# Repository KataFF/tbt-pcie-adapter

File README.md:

# Thunderbolt to PCIe Adapter

Copyright (c) 2022-2024 [Antmicro](https://www.antmicro.com) 
Original design by Antmicro up to rev. 1.0.2.
Further developed by Kajetan Wierszelis (rev. 1.0.3. and later ones)

## Overview

This project contains open hardware design files for an adapter board wrapping 4-lane (i.e. 4x) PCIe Gen 3.0 devices into a Thunderbolt 3 uplink.
It is based on the Intel/JHL6340SLLSQ Thunderbolt controller.
The design files were prepared in KiCad 7.x & updated to KiCad 8.x.

## Key features

* Intel JHL6340SLLSQ Thunderbolt 3 controller 
* PCIe x4 expansion slot
* On-board Step-Up DC-DC generating 12V (required by some PCIe cards)

## Project structure

The main directory contains KiCad PCB project files, a LICENSE, and a README.
The remaining files are stored in the following directories:

* `img` - contains graphics for this README
* `doc` - contains schematics in pdf form
* `assets` - contains visual assets for showcasing the board at [Open Hardware Portal](https://openhardware.antmicro.com)

## Licensing

This project is published under the [Apache-2.0](LICENSE) license.

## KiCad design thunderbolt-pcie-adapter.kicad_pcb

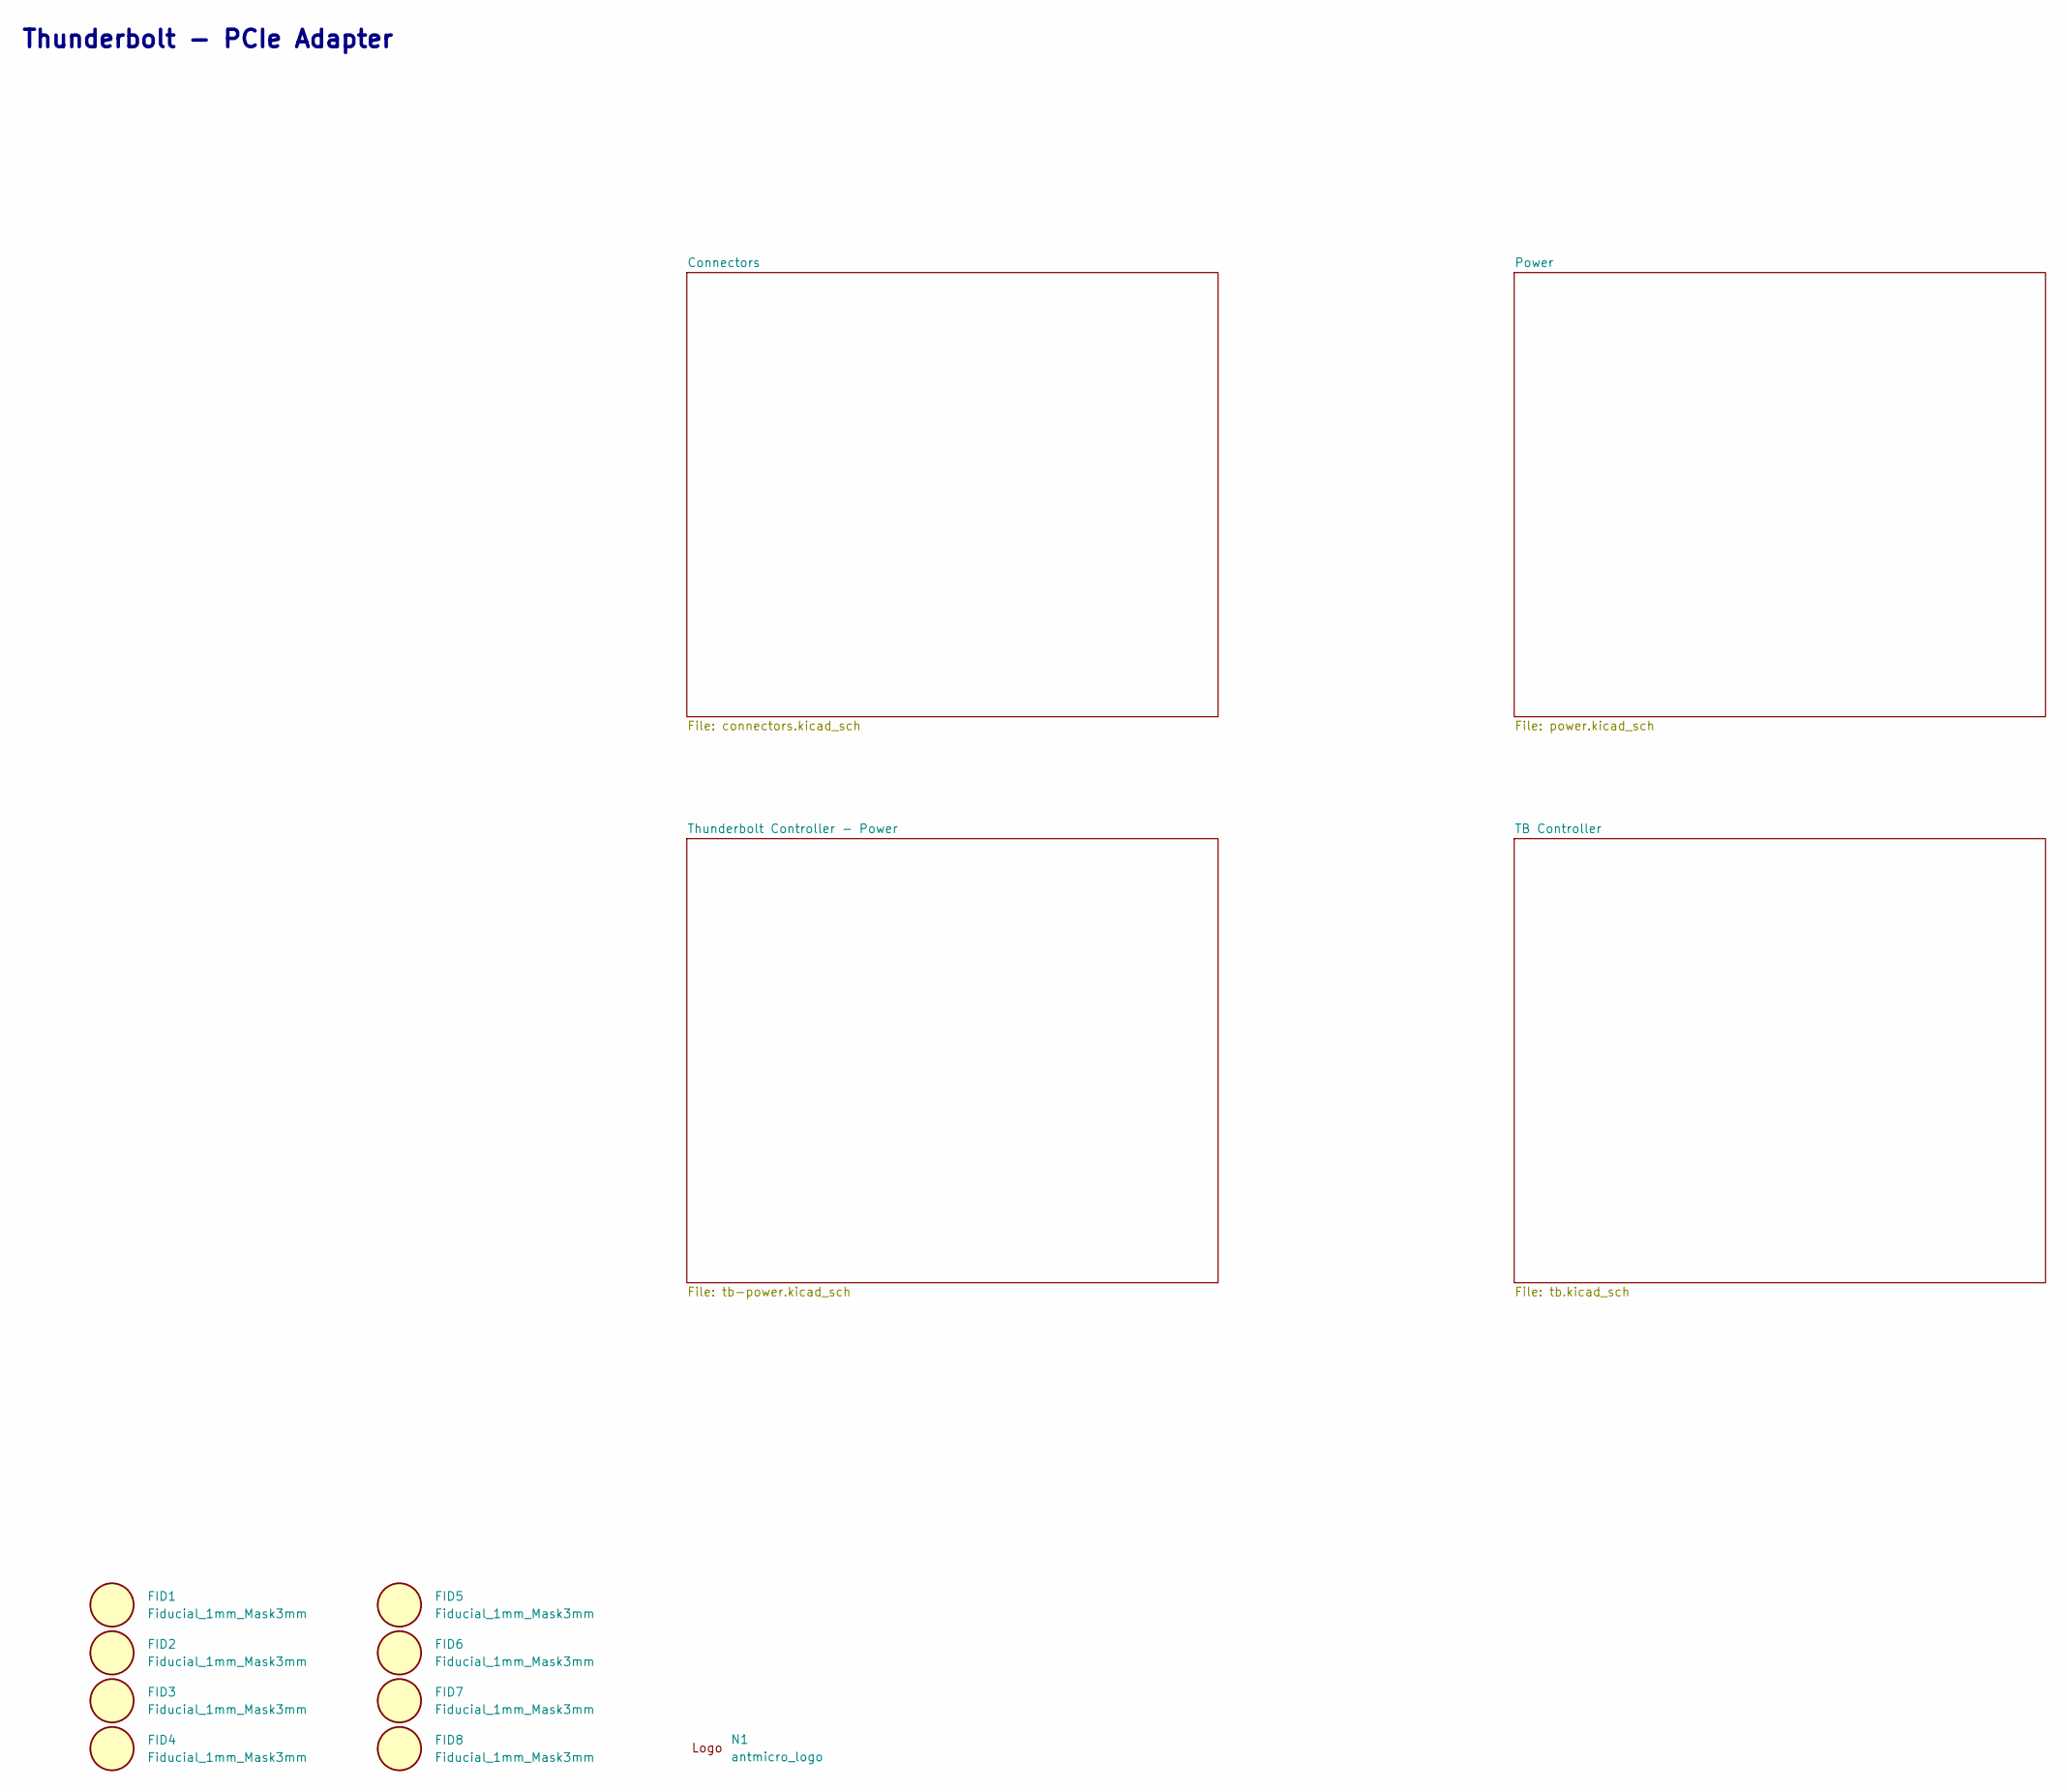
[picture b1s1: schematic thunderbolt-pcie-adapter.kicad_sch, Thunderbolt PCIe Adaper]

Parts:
FID1, FID2, FID3, FID4, FID5, FID6, FID7, FID8: Fiducial_1mm_Mask3mm
N1: antmicro_logo; antmicro-logo_scaled_12mm_mask

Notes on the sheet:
Thunderbolt - PCIe Adapter

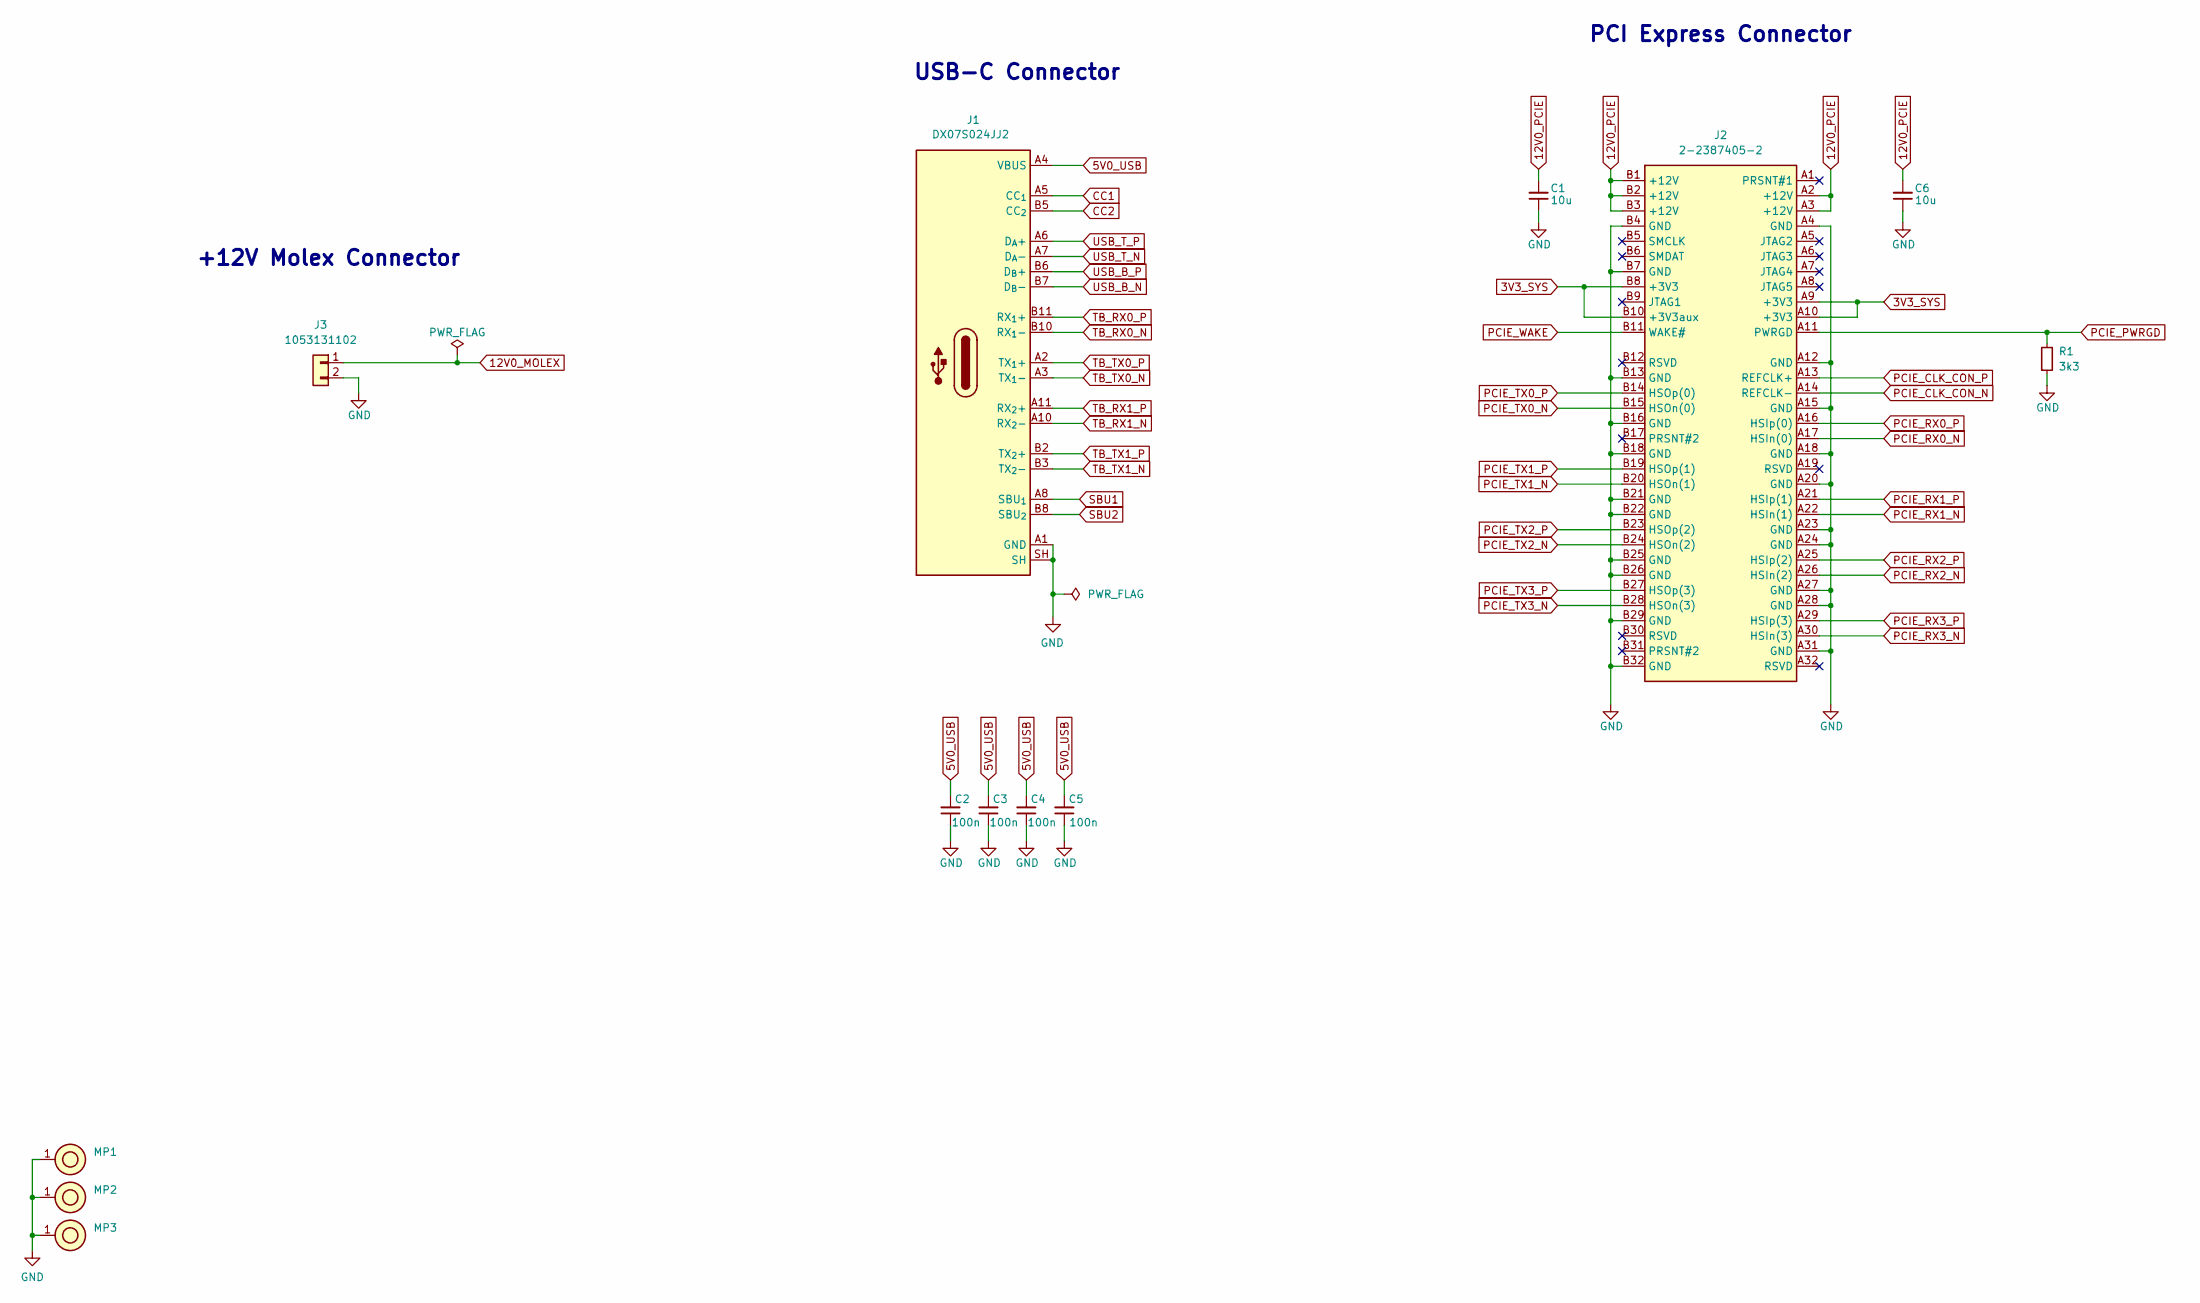
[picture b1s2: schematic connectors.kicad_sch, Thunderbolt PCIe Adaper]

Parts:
C1, C6: C_10u_0805_35V; C_0805_2012Metric; Voltage 35V; MPN GRM21BR6YA106KE43L
C2, C3, C4, C5: C_100n_0402; C_0402_1005Metric; Voltage 50V; MPN GRM155R61H104KE14D
J1: USB-C_JAE_DX07S024JJ2; USB-C_Receptacle_JAE_DX07S024JJ2; MPN DX07S024JJ2
J2: PCIe_x4_Conn_EdgeMount_Open; PCIE_TE_2-2387405-2; MPN 2-2387405-2
J3: Molex_Nano-Fit_1x2_1053131102; Conn_Molex_Nano-Fit_1x2_1053131102; MPN 1053131102
MP1, MP2, MP3: MP_Pad6mm_Drill3mm
R1: R_3k3_0402; R_0402_1005Metric; Tolerance 1%; MPN CR0402-FX-3301GLF

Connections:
3V3_SYS: J2.A9 (+3V3), J2.A10 (+3V3), J2.B8 (+3V3), J2.B10 (+3V3aux); also elsewhere on the board
5V0_USB: C2.2, C3.2, C4.2, C5.2, J1.A4 (VBUS), J1.A9 (VBUS), J1.B4 (VBUS), J1.B9 (VBUS); also elsewhere on the board
12V0_MOLEX: J3.1; also elsewhere on the board
12V0_PCIE: C1.2, C6.2, J2.A2 (+12V), J2.A3 (+12V), J2.B1 (+12V), J2.B2 (+12V), J2.B3 (+12V); also elsewhere on the board
CC1: J1.A5 (CC_{1}); also elsewhere on the board
CC2: J1.B5 (CC_{2}); also elsewhere on the board
GND: C1.1, C2.1, C3.1, C4.1, C5.1, C6.1, J1.A1 (GND), J1.A12 (GND), J1.B1 (GND), J1.B12 (GND), J1.SH, J2.A4 (GND), J2.A12 (GND), J2.A15 (GND), J2.A18 (GND), J2.A20 (GND), J2.A23 (GND), J2.A24 (GND), J2.A27 (GND), J2.A28 (GND), J2.A31 (GND), J2.B4 (GND), J2.B7 (GND), J2.B13 (GND), J2.B16 (GND), J2.B18 (GND), J2.B21 (GND), J2.B22 (GND), J2.B25 (GND), J2.B26 (GND), J2.B29 (GND), J2.B32 (GND), J3.2, MP1.1, MP2.1, MP3.1, R1.1; also elsewhere on the board
PCIE_CLK_CON_N: J2.A14 (REFCLK-); also elsewhere on the board
PCIE_CLK_CON_P: J2.A13 (REFCLK+); also elsewhere on the board
PCIE_PWRGD: J2.A11 (PWRGD), R1.2; also elsewhere on the board
PCIE_RX0_N: J2.A17 (HSIn(0)); also elsewhere on the board
PCIE_RX0_P: J2.A16 (HSIp(0)); also elsewhere on the board
PCIE_RX1_N: J2.A22 (HSIn(1)); also elsewhere on the board
PCIE_RX1_P: J2.A21 (HSIp(1)); also elsewhere on the board
PCIE_RX2_N: J2.A26 (HSIn(2)); also elsewhere on the board
PCIE_RX2_P: J2.A25 (HSIp(2)); also elsewhere on the board
PCIE_RX3_N: J2.A30 (HSIn(3)); also elsewhere on the board
PCIE_RX3_P: J2.A29 (HSIp(3)); also elsewhere on the board
PCIE_TX0_N: J2.B15 (HSOn(0)); also elsewhere on the board
PCIE_TX0_P: J2.B14 (HSOp(0)); also elsewhere on the board
PCIE_TX1_N: J2.B20 (HSOn(1)); also elsewhere on the board
PCIE_TX1_P: J2.B19 (HSOp(1)); also elsewhere on the board
PCIE_TX2_N: J2.B24 (HSOn(2)); also elsewhere on the board
PCIE_TX2_P: J2.B23 (HSOp(2)); also elsewhere on the board
PCIE_TX3_N: J2.B28 (HSOn(3)); also elsewhere on the board
PCIE_TX3_P: J2.B27 (HSOp(3)); also elsewhere on the board
PCIE_WAKE: J2.B11 (WAKE#); also elsewhere on the board
SBU1: J1.A8 (SBU_{1}); also elsewhere on the board
SBU2: J1.B8 (SBU_{2}); also elsewhere on the board
TB_RX0_N: J1.B10 (RX_{1}-); also elsewhere on the board
TB_RX0_P: J1.B11 (RX_{1}+); also elsewhere on the board
TB_RX1_N: J1.A10 (RX_{2}-); also elsewhere on the board
TB_RX1_P: J1.A11 (RX_{2}+); also elsewhere on the board
TB_TX0_N: J1.A3 (TX_{1}-); also elsewhere on the board
TB_TX0_P: J1.A2 (TX_{1}+); also elsewhere on the board
TB_TX1_N: J1.B3 (TX_{2}-); also elsewhere on the board
TB_TX1_P: J1.B2 (TX_{2}+); also elsewhere on the board
USB_B_N: J1.B7 (D_{B}-); also elsewhere on the board
USB_B_P: J1.B6 (D_{B}+); also elsewhere on the board
USB_T_N: J1.A7 (D_{A}-); also elsewhere on the board
USB_T_P: J1.A6 (D_{A}+); also elsewhere on the board

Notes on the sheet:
+12V Molex Connector
PCI Express Connector
USB-C Connector

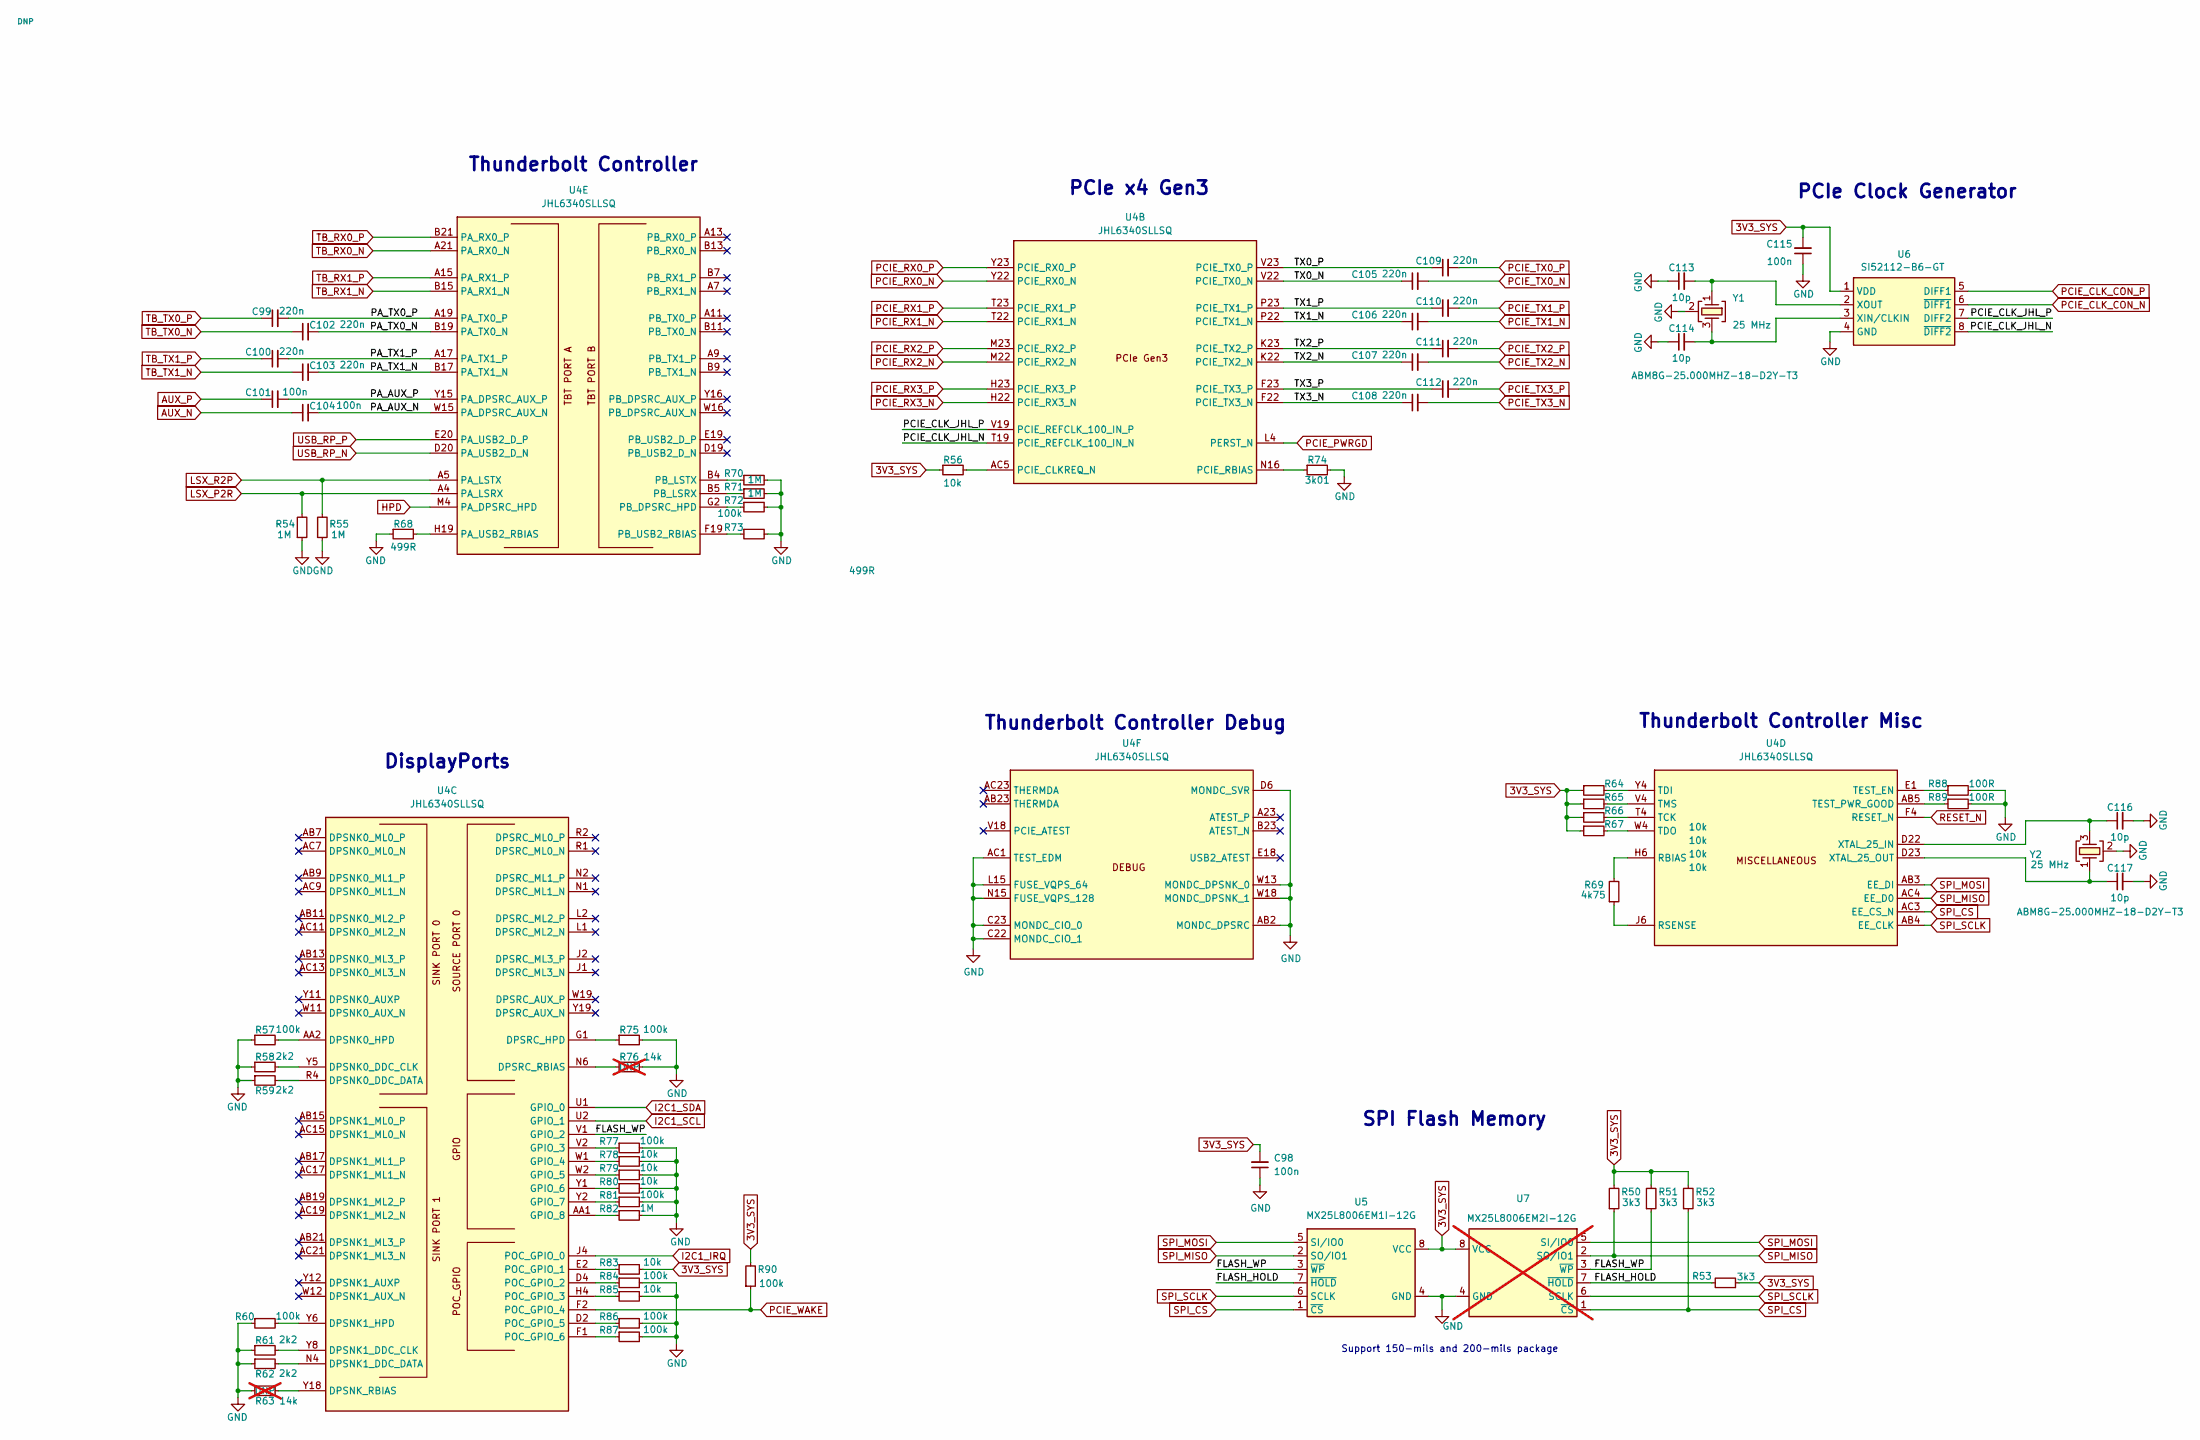
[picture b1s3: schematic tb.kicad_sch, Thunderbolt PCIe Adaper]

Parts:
C98, C101, C104, C115: C_100n_0402; C_0402_1005Metric; Voltage 50V; MPN GRM155R61H104KE14D
C99, C100, C102, C103, C105, C106, C107, C108, C109, C110, C111, C112: C_220n_0402; C_0402_1005Metric; MPN CC0402KRX5R6BB224
C113, C114, C116, C117: C_10p_0402; C_0402_1005Metric; Voltage 50V; MPN GCM1555C1H100GA16D
R50, R51, R52, R53: R_3k3_0402; R_0402_1005Metric; Tolerance 1%; MPN CR0402-FX-3301GLF
R54, R55, R70, R71, R82: R_1M_0402; R_0402_1005Metric; Tolerance 1%; MPN CR0402-FX-1004GLF
R56, R64, R65, R66, R67, R78, R79, R80, R83, R85: R_10k_0402; R_0402_1005Metric; Tolerance 1%; MPN CR0402-FX-1002GLF
R57, R60, R72, R75, R77, R81, R84, R86, R87, R90: R_100k_0402; R_0402_1005Metric; Tolerance 1%; MPN CR0402-FX-1003GLF
R58, R59, R61, R62: R_2k2_0402; R_0402_1005Metric; Tolerance 1%; MPN CR0402-FX-2201GLF
R63, R76: R_14k_0402; R_0402_1005Metric; Tolerance 1%; MPN CR0402-FX-1402GLF; not fitted
R68, R73: R_499R_0402; R_0402_1005Metric; Tolerance 1%; MPN CR0402-FX-4990GLF
R69: R_4k75_0.5%_0402; R_0402_1005Metric; Tolerance 0.5%; MPN ERJ-H2RD4751X
R74: R_3k01_0402; R_0402_1005Metric; Tolerance 1%; MPN CR0402-FX-3011GLF
R88, R89: R_100R_0402; R_0402_1005Metric; Tolerance 1%; MPN CR0402-FX-1000GLF
U4: JHL6340SLLSQ; MPN JHL6340SLLSQ
U5: MX25L8006EM1I-12G; SOIC-8_3.9x4.9x1.75mm_P1.27mm; MPN MX25L8006EM1I-12G
U6: SI52112-B6-GT; TSSOP-8_3x4.4mm_P0.65mm; MPN SI52112-B6-GT
U7: MX25L8006EM2I-12G; SOIC-8_5.3x5.3x2mm_P1.27mm; MPN MX25L8006EM2I-12G; not fitted
Y1, Y2: Resonator_25MHz_ABM8G; Resonator_SMD_Abracon_ABM8G_3.2x2.5mm; MPN ABM8G-25.000MHZ-18-D2Y-T3

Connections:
3V3_SYS: C98.2, C115.2, R50.2, R51.2, R52.2, R53.1, R56.1, R64.1, R65.1, R66.1, R67.1, R83.2, R90.2, U5.8 (VCC), U6.1 (VDD), U7.8 (VCC); also elsewhere on the board
/TB Controller/FLASH_HOLD: R53.2, U5.7 (~HOLD), U7.7 (~HOLD)
/TB Controller/FLASH_WP: R51.1, U4.V1 (GPIO_2), U5.3 (~WP), U7.3 (~WP)
/TB Controller/PA_AUX_N: C104.2, U4.W15 (PA_DPSRC_AUX_N)
/TB Controller/PA_AUX_P: C101.2, U4.Y15 (PA_DPSRC_AUX_P)
/TB Controller/PA_TX0_N: C102.2, U4.B19 (PA_TX0_N)
/TB Controller/PA_TX0_P: C99.2, U4.A19 (PA_TX0_P)
/TB Controller/PA_TX1_N: C103.2, U4.B17 (PA_TX1_N)
/TB Controller/PA_TX1_P: C100.2, U4.A17 (PA_TX1_P)
/TB Controller/PCIE_CLK_JHL_N: U4.T19 (PCIE_REFCLK_100_IN_N), U6.8 (~DIFF2)
/TB Controller/PCIE_CLK_JHL_P: U4.V19 (PCIE_REFCLK_100_IN_P), U6.7 (DIFF2)
/TB Controller/TX0_N: C105.1, U4.V22 (PCIE_TX0_N)
/TB Controller/TX0_P: C109.1, U4.V23 (PCIE_TX0_P)
/TB Controller/TX1_N: C106.1, U4.P22 (PCIE_TX1_N)
/TB Controller/TX1_P: C110.1, U4.P23 (PCIE_TX1_P)
/TB Controller/TX2_N: C107.1, U4.K22 (PCIE_TX2_N)
/TB Controller/TX2_P: C111.1, U4.K23 (PCIE_TX2_P)
/TB Controller/TX3_N: C108.1, U4.F22 (PCIE_TX3_N)
/TB Controller/TX3_P: C112.1, U4.F23 (PCIE_TX3_P)
AUX_N: C104.1; also elsewhere on the board
AUX_P: C101.1; also elsewhere on the board
GND: C98.1, C113.1, C114.1, C115.1, C116.2, C117.2, R54.1, R55.1, R57.1, R58.1, R59.1, R60.1, R61.1, R62.1, R63.1, R68.1, R70.2, R71.2, R72.2, R73.2, R74.2, R75.2, R76.2, R77.2, R78.2, R79.2, R80.2, R81.2, R82.2, R84.2, R85.2, R86.2, R87.2, R88.2, R89.2, U4.AB2 (MONDC_DPSRC), U4.AC1 (TEST_EDM), U4.C22 (MONDC_CIO_1), U4.C23 (MONDC_CIO_0), U4.D6 (MONDC_SVR), U4.L15 (FUSE_VQPS_64), U4.N15 (FUSE_VQPS_128), U4.W13 (MONDC_DPSNK_0), U4.W18 (MONDC_DPSNK_1), U5.4 (GND), U6.4 (GND), U7.4 (GND), Y1.2 (SH), Y1.4 (SH), Y2.2 (SH), Y2.4 (SH); also elsewhere on the board
HPD: U4.M4 (PA_DPSRC_HPD); also elsewhere on the board
I2C1_IRQ: U4.J4 (POC_GPIO_0); also elsewhere on the board
I2C1_SCL: U4.U2 (GPIO_1); also elsewhere on the board
I2C1_SDA: U4.U1 (GPIO_0); also elsewhere on the board
LSX_P2R: R54.2, U4.A4 (PA_LSRX); also elsewhere on the board
LSX_R2P: R55.2, U4.A5 (PA_LSTX); also elsewhere on the board
unnamed: R56.2, U4.AC5 (PCIE_CLKREQ_N)
unnamed: R74.1, U4.N16 (PCIE_RBIAS)
unnamed: R58.2, U4.Y5 (DPSNK0_DDC_CLK)
unnamed: R59.2, U4.R4 (DPSNK0_DDC_DATA)
unnamed: R57.2, U4.AA2 (DPSNK0_HPD)
unnamed: R61.2, U4.Y8 (DPSNK1_DDC_CLK)
unnamed: R62.2, U4.N4 (DPSNK1_DDC_DATA)
unnamed: R60.2, U4.Y6 (DPSNK1_HPD)
unnamed: R63.2, U4.Y18 (DPSNK_RBIAS)
unnamed: R75.1, U4.G1 (DPSRC_HPD)
unnamed: R76.1, U4.N6 (DPSRC_RBIAS)
unnamed: R77.1, U4.V2 (GPIO_3)
unnamed: R78.1, U4.W1 (GPIO_4)
unnamed: R79.1, U4.W2 (GPIO_5)
unnamed: R80.1, U4.Y1 (GPIO_6)
unnamed: R81.1, U4.Y2 (GPIO_7)
unnamed: R82.1, U4.AA1 (GPIO_8)
unnamed: R83.1, U4.E2 (POC_GPIO_1)
unnamed: R84.1, U4.D4 (POC_GPIO_2)
unnamed: R85.1, U4.H4 (POC_GPIO_3)
unnamed: R86.1, U4.D2 (POC_GPIO_5)
unnamed: R87.1, U4.F1 (POC_GPIO_6)
unnamed: R69.2, U4.H6 (RBIAS)
unnamed: R69.1, U4.J6 (RSENSE)
unnamed: R66.2, U4.T4 (TCK)
unnamed: R64.2, U4.Y4 (TDI)
unnamed: R67.2, U4.W4 (TDO)
unnamed: R88.1, U4.E1 (TEST_EN)
unnamed: R89.1, U4.AB5 (TEST_PWR_GOOD)
unnamed: R65.2, U4.V4 (TMS)
unnamed: C116.1, U4.D22 (XTAL_25_IN), Y2.3
unnamed: C117.1, U4.D23 (XTAL_25_OUT), Y2.1
unnamed: R68.2, U4.H19 (PA_USB2_RBIAS)
unnamed: R72.1, U4.G2 (PB_DPSRC_HPD)
unnamed: R71.1, U4.B5 (PB_LSRX)
unnamed: R70.1, U4.B4 (PB_LSTX)
unnamed: R73.1, U4.F19 (PB_USB2_RBIAS)
unnamed: C114.2, U6.3 (XIN/CLKIN), Y1.3
unnamed: C113.2, U6.2 (XOUT), Y1.1
PCIE_CLK_CON_N: U6.6 (~DIFF1); also elsewhere on the board
PCIE_CLK_CON_P: U6.5 (DIFF1); also elsewhere on the board
PCIE_PWRGD: U4.L4 (PERST_N); also elsewhere on the board
PCIE_RX0_N: U4.Y22 (PCIE_RX0_N); also elsewhere on the board
PCIE_RX0_P: U4.Y23 (PCIE_RX0_P); also elsewhere on the board
PCIE_RX1_N: U4.T22 (PCIE_RX1_N); also elsewhere on the board
PCIE_RX1_P: U4.T23 (PCIE_RX1_P); also elsewhere on the board
PCIE_RX2_N: U4.M22 (PCIE_RX2_N); also elsewhere on the board
PCIE_RX2_P: U4.M23 (PCIE_RX2_P); also elsewhere on the board
PCIE_RX3_N: U4.H22 (PCIE_RX3_N); also elsewhere on the board
PCIE_RX3_P: U4.H23 (PCIE_RX3_P); also elsewhere on the board
PCIE_TX0_N: C105.2; also elsewhere on the board
PCIE_TX0_P: C109.2; also elsewhere on the board
PCIE_TX1_N: C106.2; also elsewhere on the board
PCIE_TX1_P: C110.2; also elsewhere on the board
PCIE_TX2_N: C107.2; also elsewhere on the board
PCIE_TX2_P: C111.2; also elsewhere on the board
PCIE_TX3_N: C108.2; also elsewhere on the board
PCIE_TX3_P: C112.2; also elsewhere on the board
PCIE_WAKE: R90.1, U4.F2 (POC_GPIO_4); also elsewhere on the board
RESET_N: U4.F4 (RESET_N); also elsewhere on the board
SPI_CS: R52.1, U4.AC3 (EE_CS_N), U5.1 (~CS), U7.1 (~CS); also elsewhere on the board
SPI_MISO: R50.1, U4.AC4 (EE_D0), U5.2 (SO/IO1), U7.2 (SO/IO1); also elsewhere on the board
SPI_MOSI: U4.AB3 (EE_DI), U5.5 (SI/IO0), U7.5 (SI/IO0); also elsewhere on the board
SPI_SCLK: U4.AB4 (EE_CLK), U5.6 (SCLK), U7.6 (SCLK); also elsewhere on the board
TB_RX0_N: U4.A21 (PA_RX0_N); also elsewhere on the board
TB_RX0_P: U4.B21 (PA_RX0_P); also elsewhere on the board
TB_RX1_N: U4.B15 (PA_RX1_N); also elsewhere on the board
TB_RX1_P: U4.A15 (PA_RX1_P); also elsewhere on the board
TB_TX0_N: C102.1; also elsewhere on the board
TB_TX0_P: C99.1; also elsewhere on the board
TB_TX1_N: C103.1; also elsewhere on the board
TB_TX1_P: C100.1; also elsewhere on the board
USB_RP_N: U4.D20 (PA_USB2_D_N); also elsewhere on the board
USB_RP_P: U4.E20 (PA_USB2_D_P); also elsewhere on the board

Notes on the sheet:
DisplayPorts
Thunderbolt Controller Misc
PCIe Clock Generator
SPI Flash Memory
Thunderbolt Controller
Thunderbolt Controller Debug
Support 150-mils and 200-mils package
PCIe x4 Gen3

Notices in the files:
parts and their libraries:
License: Apache-2.0
